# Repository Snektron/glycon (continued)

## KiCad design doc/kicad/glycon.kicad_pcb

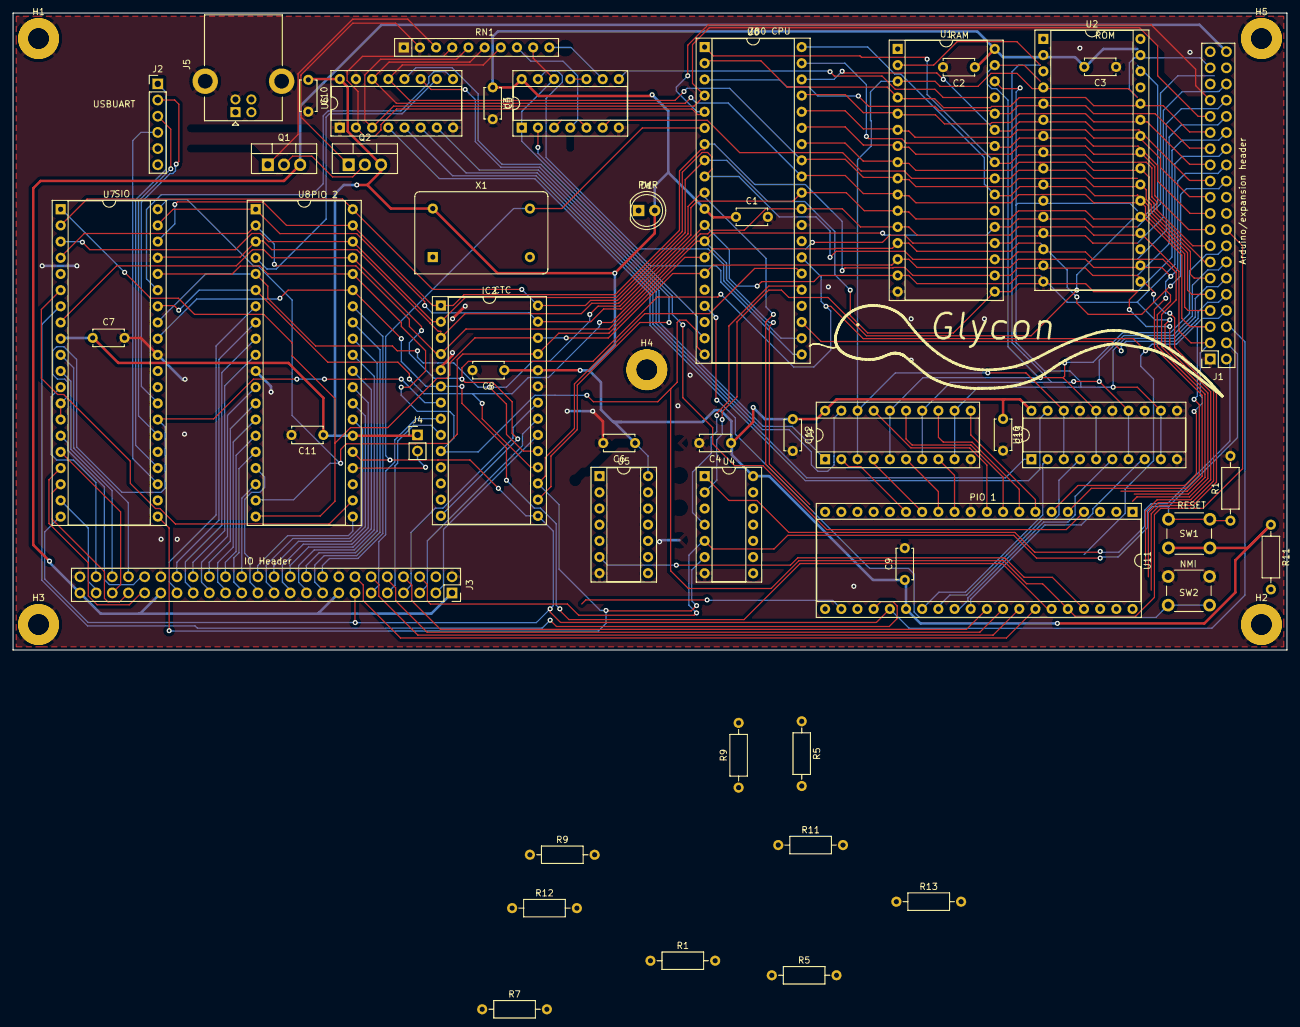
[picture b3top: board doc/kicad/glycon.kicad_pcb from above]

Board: 2 copper layers, 200.0 x 100.0 mm, 59 parts (0 on the bottom side), 125 nets.

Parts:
C1, C2, C3, C4, C5, C6, C7, C8, C9, C10, C11, C12, C13: 100nF; C_Disc_D4.7mm_W2.5mm_P5.00mm
D1: LED; LED_D5.0mm
H1, H1#2, H2, H2#2, H3, H3#2, H4, H4#2, H5, H5#2: MountingHole_Pad; MountingHole_3.2mm_M3_Pad
IC2: CTC-DIP-28; DIP-28_W15.24mm_Socket
J1: Arduino/system bus header; PinSocket_2x20_P2.54mm_Vertical
J2: PMOD USBUART conn; PinHeader_1x06_P2.54mm_Vertical
J3: Conn_02x24_Odd_Even; PinSocket_2x24_P2.54mm_Vertical
J4: Conn_01x02; PinHeader_1x02_P2.54mm_Vertical
J5: USB_B; USB_B_Lumberg_2411_02_Horizontal
Q1, Q2: IRF9540N; TO-220-3_Vertical
R1, R1#2, R5, R5#2, R7, R9, R9#2, R11, R11#2, R13: 10K; R_Axial_DIN0207_L6.3mm_D2.5mm_P10.16mm_Horizontal
R12: 470; R_Axial_DIN0207_L6.3mm_D2.5mm_P10.16mm_Horizontal
RN1: 10K; R_Array_SIP10
SW1, SW2: SW_Push; SW_PUSH_6mm
U0: Z80CPU; DIP-40_W15.24mm_Socket
U1: 628128_DIP32_SSOP32; DIP-32_W15.24mm_Socket
U2: SST39SF010; DIP-32_W15.24mm_Socket
U3: 74HC32; DIP-14_W7.62mm_Socket
U4: 74HC04; DIP-14_W7.62mm_Socket
U5: 74LS08; DIP-14_W7.62mm_Socket
U6: 74LS139; DIP-16_W7.62mm_Socket
U7: SIO0-DIP-40; DIP-40_W15.24mm_Socket
U8, U11: PIO-DIP-40; DIP-40_W15.24mm_Socket
U9, U10: 74HC244; DIP-20_W7.62mm_Socket
X1: ACO-6.144MHz; Oscillator_DIP-14

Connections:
+5V: J1.40, J2.6, J3.1, J3.15, J3.37, J3.47, J5.1 (VBUS), Q1.3 (S)
/A0: IC2.18 (CS0), J1.3, U0.30 (A0), U1.12 (A0), U2.12 (A0), U7.34 (B/~A), U8.6 (B/~A), U11.6 (B/~A)
/A1: IC2.19 (CS1), J1.5, U0.31 (A1), U1.11 (A1), U2.11 (A1), U7.33 (C/~D), U8.5 (C/~D), U11.5 (C/~D)
/A2: J1.7, RN1.6 (R5.2), U0.32 (A2), U1.10 (A2), U2.10 (A2), U6.14 (A0)
/A3: J1.11, RN1.7 (R6.2), U0.33 (A3), U1.9 (A3), U2.9 (A3), U6.13 (A1)
/A4: J1.13, U0.34 (A4), U1.8 (A4), U2.8 (A4)
/A5: J1.17, U0.35 (A5), U1.7 (A5), U2.7 (A5)
/A6: J1.21, U0.36 (A6), U1.6 (A6), U2.6 (A6)
/A7: J1.25, U0.37 (A7), U1.5 (A7), U2.5 (A7)
/A8: J1.23, U0.38 (A8), U1.27 (A8), U2.27 (A8)
/A9: J1.19, U0.39 (A9), U1.26 (A9), U2.26 (A9)
/A10: J1.9, U0.40 (A10), U1.23 (A10), U2.23 (A10)
/A11: J1.15, U0.1 (A11), U1.25 (A11), U2.25 (A11)
/A12: J1.29, U0.2 (A12), U1.4 (A12), U2.4 (A12)
/A13: J1.27, U0.3 (A13), U1.28 (A13), U2.28 (A13)
/A14: J1.16, J1.37, U1.3 (A14), U2.29 (A14), U9.3 (2Y0), U9.18 (1Y0), U10.3 (2Y0), U10.18 (1Y0)
/A15: J1.14, U1.31 (A15), U2.3 (A15), U9.5 (2Y1), U9.16 (1Y1), U10.5 (2Y1), U10.16 (1Y1)
/A16: J1.12, U1.2 (A16), U2.2 (A16), U9.7 (2Y2), U9.14 (1Y2), U10.7 (2Y2), U10.14 (1Y2)
/A17: U1.30 (CS2), U2.22 (~CE), U9.9 (2Y3), U9.12 (1Y3), U10.9 (2Y3), U10.12 (1Y3)
/ARDY: J3.28, U8.18 (ARDY)
/BRDY: J3.26, U8.21 (BRDY)
/BUSRQ: J1.35, R9.2, R9#2.2, U4.3
/CLK: IC2.15 (CLK), J1.6, J3.13, U0.6 (~CLK), U7.20 (Φ), U8.25 (CLK), U11.25 (CLK), X1.8 (OUT)
/CT1: IC2.22 (CLK/TRG1), J3.7
/CT2: IC2.21 (CLK/TRG2), J3.5
/CT3: IC2.20 (CLK/TRG3), J3.3
/CTSB: J2.4, U7.23 (~CTSB)
/D0: IC2.25 (D0), J1.24, U0.14 (D0), U1.13 (Q0), U2.13 (D0), U7.40 (D0), U8.19 (D0), U11.19 (D0)
/D1: IC2.26 (D1), J1.26, U0.15 (D1), U1.14 (Q1), U2.14 (D1), U7.1 (D1), U8.20 (D1), U11.20 (D1)
/D2: IC2.27 (D2), J1.28, U0.12 (D2), U1.15 (Q2), U2.15 (D2), U7.39 (D2), U8.1 (D2), U11.1 (D2)
/D3: IC2.28 (D3), J1.30, U0.8 (D3), U1.17 (Q3), U2.17 (D3), U7.2 (D3), U8.40 (D3), U11.40 (D3)
/D4: IC2.1 (D4), J1.32, U0.7 (D4), U1.18 (Q4), U2.18 (D4), U7.38 (D4), U8.39 (D4), U11.39 (D4)
/D5: IC2.2 (D5), J1.34, U0.9 (D5), U1.19 (Q5), U2.19 (D5), U7.3 (D5), U8.38 (D5), U11.38 (D5)
/D6: IC2.3 (D6), J1.36, U0.10 (D6), U1.20 (Q6), U2.20 (D6), U7.37 (D6), U8.3 (D6), U11.3 (D6)
/D7: IC2.4 (D7), J1.38, U0.13 (D7), U1.21 (Q7), U2.21 (D7), U7.4 (D7), U8.2 (D7), U11.2 (D7)
/IEI0: IC2.13 (IEI), U11.22 (IEO)
/IEI1: U7.7 (IEO), U11.24 (IEI)
/IEI2: U7.6 (IEI), U8.22 (IEO)
/IEI3: J4.2, U8.24 (IEI)
/PA0: J3.30, U8.15 (PA0)
/PA1: J3.29, U8.14 (PA1)
/PA2: J3.32, U8.13 (PA2)
/PA3: J3.31, U8.12 (PA3)
/PA4: J3.34, U8.10 (PA4)
/PA5: J3.33, U8.9 (PA5)
/PA6: J3.36, U8.8 (PA6)
/PA7: J3.35, U8.7 (PA7)
/PB0: J3.23, U8.27 (PB0)
/PB1: J3.24, U8.28 (PB1)
/PB2: J3.21, U8.29 (PB2)
/PB3: J3.22, U8.30 (PB3)
/PB4: J3.19, U8.31 (PB4)
/PB5: J3.20, U8.32 (PB5)
/PB6: J3.17, U8.33 (PB6)
/PB7: J3.18, U8.34 (PB7)
/PC0: J3.14, U11.34 (PB7)
/PC1: J3.12, U11.33 (PB6)
/PC2: J3.10, U11.32 (PB5)
/PC3: J3.8, U11.31 (PB4)
/PGA0: J1.31, RN1.5 (R4.2), U0.4 (A14), U6.3 (A1)
/PGA1: J1.33, RN1.4 (R3.2), U0.5 (A15), U6.2 (A0)
/RAM WE: J1.22, RN1.10 (R9.2), U3.9
/RAM/ROM OE: J1.20, RN1.8 (R7.2), U3.4
/RESET: J1.4, J3.6, R1.1, R1#2.1, SW1.2, U4.5
/ROM WE: J1.2, R5.2, R5#2.2, U4.1
/RTSB: J2.1, U7.24 (~RTSB)
/RXDA: J3.46, U7.12 (RXDA)
/RxDB: J2.2, U7.28 (RXDB)
/SERCLK: IC2.7 (ZC/TO0), U7.13 (~RXCA), U7.14 (~TXCA), U7.27 (~RxTxCB)
/SYNCA: J3.44, U7.11 (~SYNCA)
/TO1: IC2.8 (ZC/TO1), J3.11
/TO2: IC2.9 (ZC/TO2), J3.9
/TXDA: J3.40, U7.15 (TXDA)
/TxDB: J2.3, U7.26 (TXDB)
/~ASTB: J3.27, U8.16 (~ASTB)
/~BSTB: J3.25, U8.17 (~BSTB)
/~BUSACK: J1.10, U0.23 (~BUSACK)
/~CTSA: J3.41, U7.18 (~CTSA)
/~DCDA: J3.45, U7.19 (~DCDA)
/~DTRA: J3.43, U7.16 (~DTRA)
/~INTIN: J1.39, R7.2, U5.1
/~INT: U0.16 (~INT), U5.3
/~IORD: IC2.6 (~RD), U0.21 (~RD), U3.2, U7.32 (~RD), U8.35 (~RD), U11.35 (~RD)
/~IORQ: IC2.10 (~IORQ), J1.18, U0.20 (~IORQ), U7.36 (~IORQ), U8.36 (~IORQ), U11.36 (~IORQ)
/~IO_EN1: U6.9 (O3), U7.35 (~CE)
/~M1: IC2.14 (~M1), J1.8, U0.27 (~M1), U5.4, U7.8 (~M1)
/~MEMRD: U1.24 (~OE), U2.24 (~OE), U3.6
/~NMI: R11.2, R11#2.2, SW2.2, U0.17 (~NMI)
/~PIO_M1: U5.6, U8.37 (~M1), U11.37 (~M1)
/~RESET: IC2.17 (~RESET), U0.26 (~RESET), U4.6, U5.5, U7.21 (~RESET)
/~RTSA: J3.39, U7.17 (~RTSA)
/~W/~RDYA: J3.42, U7.10 (~W/~RDYA)
Earth: C1.2, C2.2, C3.1, C4.2, C5.2, C6.2, C7.2, C8.2, C9.2, C10.2, C11.2, C12.2, C13.2, H1.1, H1#2.1, H2.1, H2#2.1, H3.1, H3#2.1, H4.1, H4#2.1, H5.1, H5#2.1, IC2.5 (GND), IC2.23 (CLK/TRG0), J1.1, J2.5, J3.2, J3.16, J3.38, J3.48, J5.4 (GND), J5.5 (Shield), R1.2, R1#2.2, R5.1, R5#2.1, R9.1, R9#2.1, R12.2, SW2.1, U0.29 (GND), U1.16 (GND), U1.22 (~CS1), U2.16 (GND), U3.7 (GND), U4.7 (GND), U5.7 (GND), U6.1 (E), U6.8 (GND), U6.15 (E), U7.31 (GND), U8.11 (GND), U9.10 (GND), U10.10 (GND), U10.11 (2A3), U10.13 (2A2), U10.15 (2A1), U10.17 (2A0), U11.11 (GND)
unnamed: D1.1 (K), R12.1
unnamed: IC2.12 (~INT), R13.2, U5.2, U7.5 (~INT), U8.23 (~INT), U11.23 (~INT)
unnamed: IC2.16 (~CE), U6.11 (O1)
unnamed: Q1.1 (G), RN1.3 (R2.2)
unnamed: Q1.2 (D), Q2.2 (D)
unnamed: Q2.1 (G), RN1.2 (R1.2)
unnamed: RN1.9 (R8.2), U0.19 (~MREQ), U3.1, U3.12
unnamed: U0.22 (~WR), U3.13
unnamed: U0.25 (~BUSRQ), U4.4
unnamed: U1.29 (~WE), U3.8
unnamed: U2.31 (~WE), U4.2
unnamed: U3.3, U3.5
unnamed: U3.10, U3.11
unnamed: U6.6 (O2), U9.19 (2OE)
unnamed: U6.7 (O3), U9.1 (1OE)
unnamed: U6.10 (O2), U8.4 (~CE)
unnamed: U6.5 (O1), U10.1 (1OE)
unnamed: U10.2 (1A0), U11.27 (PB0)
unnamed: U10.4 (1A1), U11.28 (PB1)
unnamed: U10.6 (1A2), U11.29 (PB2)
unnamed: U10.8 (1A3), U11.30 (PB3)
unnamed: U6.4 (O0), U10.19 (2OE)
unnamed: U6.12 (O0), U11.4 (~CE)
unnamed: U9.11 (2A3), U11.7 (PA7)
unnamed: U9.13 (2A2), U11.8 (PA6)
unnamed: U9.15 (2A1), U11.9 (PA5)
unnamed: U9.17 (2A0), U11.10 (PA4)
unnamed: U9.8 (1A3), U11.12 (PA3)
unnamed: U9.6 (1A2), U11.13 (PA2)
unnamed: U9.4 (1A1), U11.14 (PA1)
unnamed: U9.2 (1A0), U11.15 (PA0)
VDD: C1.1, C2.1, C3.2, C4.1, C5.1, C6.1, C7.1, C8.1, C9.1, C10.1, C11.1, C12.1, C13.1, D1.2 (A), IC2.11 (IEO), IC2.24 (+5V), J4.1, Q2.3 (S), R7.1, R11.1, R11#2.1, R13.1, SW1.1, U0.11 (VCC), U0.24 (~WAIT), U1.32 (VCC), U2.32 (VCC), U3.14 (VCC), U4.14 (VCC), U5.14 (VCC), U6.16 (VCC), U7.9 (+5V), U8.26 (VCC), U9.20 (VCC), U10.20 (VCC), U11.26 (VCC), X1.14 (Vcc)

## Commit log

2021-07-26 Project setup & ye olde blinking led
2021-07-26 Add readme
2021-07-30 coprocessor to z80 pinout diagram
2021-08-08 Coprocessor usb serial communication
2021-08-08 Datasheet + arduino pinout
2021-08-18 change arduino to z80 bridge pinout
2021-08-19 change adapter pinout
2021-12-26 coproc: update pinout
2021-12-26 coproc: pin direction enum
2021-12-26 restructure coprocessor as a separate meson project
2021-12-26 rename coprocessor to glyco
2021-12-27 add atmega2560 docs
2021-12-27 glydb setup
2021-12-27 move manuals to dedicated doc/manuals directory
2021-12-27 glydb: basic repl loop
2021-12-29 glydb: begin command parsing
2021-12-29 glydb: use editline for reading lines
2021-12-29 glydb: more command parsing
2021-12-29 glydb: command error reporting
2021-12-29 glydb: save options & arguments
2021-12-29 glydb: improve positional arguments
2021-12-30 glydb: use pointer arrays instead of value arrays for commands
2021-12-30 glydb: help reporting setup
2021-12-30 glydb: restructure some stuff
2021-12-30 glydb: quit command
2021-12-30 glydb: improve help command
2021-12-30 glydb: connection command
2021-12-31 glydb: rename interpreter to debugger
2021-12-31 glydb: don't return a custom status for conn_open_serial; just return errno
2021-12-31 glydb: punctuation
2021-12-31 correct Z80 manual
2021-12-31 ping command
2021-12-31 use common directory for the binary debug protocol
2022-01-02 glydb: value parser
2022-01-02 glydb: restructure command parsing a bit
2022-01-02 add ram WE to pinout
2022-01-02 glydb: value parsing
2022-01-03 add mainboard electric schematic
2022-01-04 memory read/write commands
2022-01-06 begin implementing new debug packet protocol
    read/write still need to be implemented.
2022-01-06 Also update the other commands
    There are still some bugs left to be worded out.
2022-01-06 Improve some things
2022-01-07 glyco: use PINx rather than PORTx for reading pin state
2022-01-07 glyco: inline pinout functions and fix timeouts
2022-01-09 fix minor errors in schematic + add mem oe to arduino connection
2022-01-09 edit U2(ROM) symbol in schematic
2022-01-09 flash read, byte program and status
2022-01-10 glydb: separate flash command
2022-01-12 improve flash cmd handling
2022-01-13 glyco: bus managing code
2022-01-13 start handling multi-byte read/write
2022-01-13 glydb: generate flag whether command option is set
2022-01-13 add xor gates between coproc header and OE, ROM WE
2022-01-13 glydb: improve read/write functionality
2022-01-13 big fast serial
2022-01-14 flash sector/chip erase commands
2022-01-14 move glycon.h and bdbp to common directory
2022-01-14 16-bit serial read function
2022-01-14 glydb: move target-related code to target.c
2022-01-15 glydb: target flash function
2022-01-15 glydb: unify memory write and flash write code
2022-01-15 glydb: reallocation-efficient buffer type
2022-01-15 glydb: memory/flash load file
2022-01-15 fix some issues with file loading + handle new xor gate
2022-01-15 glydb: close file after reading
2022-01-15 glyco: yeet bus_init
2022-01-16 glydb: disassembler
2022-01-16 glydb: disassemble command
2022-01-16 connect busack and busrq
2022-01-19 minor schematic updates
2022-01-23 re add manual files
2022-01-24 add busrq and busack to pinout diagram
2022-01-24 blah
2022-01-24 basic kernel
2022-01-24 doc: Z80 peripheral docs
2022-01-27 expand schematic with IO devices/mainboard design
2022-01-31 more schematic work
2022-02-03 more pcb work
2022-02-05 pcb design
2022-02-06 pcb work
2022-02-07 glyco: add some missing comments
2022-02-13 finish pcb trace routing
2022-02-13 glydb: add some missing comments
2022-02-21 pcb refinement
2022-03-11 update mainboard schematic pdf and add ledmatrix project under doc
2022-03-28 add BOM
2022-03-29 rollback schematic file to kicad 6.0.4
2022-03-29 update gerber plot files
2022-04-13 update pinout schematic + add old revision of board under 'glycon_rev1.0'
2022-04-27 add missing A8 pin to pinout diagram
2022-04-27 update pinout
2022-04-29 add A14-A17 to pinout diagram
2022-04-29 Wide addresses
2022-04-29 amogus
2022-05-03 schematic fixes
2022-05-04 page pio bit reverse workaround
2022-05-04 fix disassembler 16-bit immediate endianness
2022-05-04 glydb: always read packed length in target_exec_cmd
2022-05-04 misc fixes
2022-05-07 Fix ram write enable
2022-05-07 glyos setup
2022-05-08 More schematic fixes
2022-06-03 Convert pcb file to old kicad format
2022-06-03 ok so now they should be readable by kicad stable
2022-09-17 add resistor packs
2022-09-17 add resistor pack to pcb
2023-12-02 breuh
2023-12-03 update schematic
2023-12-17 switch bus IO on coprocessor to input after bus acquisition. Also modify the test assembly a bit.
2024-03-17 cleaned up schematic
2024-03-17 create pdf of revised schematic
2024-03-17 new PCB layout and initial routing
2024-03-24 remove clangd cache
2024-03-24 add flake
2024-03-24 glydb: fix unused result warning
2024-03-24 das blinkenlichten
2024-03-24 glydb: allow passing port via cli
2024-03-24 remove ccls cache
2024-03-24 add build.zig file
    Going forward we want to write some parts in Zig,
    so set up the build system for that. This has some
    minor nuisances related to building avr images, but
    it seems to work fine.
2024-03-24 glysim: setup
2024-03-29 kicad work
2024-04-01 More pcb progress
2024-05-20 almost finalized new pcb design
2024-11-03 bump flake + make zig 0.13 compatible
2024-11-03 drop size hints from function parameters
    Turns out this requires the size to be >= 1, and thats not
    the intention here.
